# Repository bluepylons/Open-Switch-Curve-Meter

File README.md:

# About 
This is an open-source, low-cost measurement device for generating force curve measurements for MX-style switches. There are two versions - a much older Gen 1 and a newer Gen 2 design.  Force curves of various switches I've measured are in the Force curve measurements\ directory. Detailed documentation for Gen 2 is in progress and will be available [here](https://github.com/bluepylons/Open-Switch-Curve-Meter/blob/main/Gen%202%20Design/README.md).

This was designed specifically for MX switches to simplify the design and make everything cheaper and more compact, and since most of the switches I am curious about (as well as almost all new switches released today) use the MX form factor. With different switch holders it can hold other discrete switches - it was used to measure a Futaba switch, and could theoretically be used to measure Alps and other discrete swithces as well. This is not as versatile as force-curve testers built around a test stand (like [the one Haata built](https://deskthority.net/viewtopic.php?t=15133)) and can't test arbitrary keyboards like that one, but it's much cheaper to build (I spent about $200 building this, and in theory this is buildable for ~$100 if one foregoes the custom PCB and order the parts from China).

This project is licensed under the CERN OHL-S (strongly reciprocal) license for the hardware designs and the software. This is a share-alike license, and if you modify the project files you are required to also open-source your modifications. 

The force curve graphs themselves - the .ODS spreadsheets and the .PNG images of the graphs in the Force curve measurements\ folder - are licensed under [Creative Commons CC-BY 4.0](https://creativecommons.org/licenses/by/4.0/deed.en). 

# The key parts
* A linear stage. I designed around [this inexpensive $55 linear stage off Amazon](https://www.amazon.com/Sliding-Precision-Stepper-T-Shaped-Electric/dp/B07QBCG9YC/ref=sr_1_5?dchild=1&keywords=50mm%2Blinear%2Bstage&qid=1615263982&sr=8-5&th=1). You can find what appear to be identical units [on Aliexpress](https://www.aliexpress.com/item/4001272086575.html?spm=a2g0o.productlist.0.0.61906e9d3wWNyG&algo_pvid=04df7b52-bc18-4d1c-b806-9cd889c3acae&algo_expid=04df7b52-bc18-4d1c-b806-9cd889c3acae-12&btsid=0bb0623916170292735655874e869e&ws_ab_test=searchweb0_0,searchweb201602_,searchweb201603_) and elsewhere for less (if you get them from Aliexpress, make sure you buy the model with 1mm pitch (lead) on the leadscrew). Gen 2 will use the same linear stage. 
* A stepper motor. The stepper motor serves two purposes - it moves the linear stage, and also keeps track of position to plot the X-axis of the force curve. Stepper motors, as long as they aren't stalled or skip steps, move a given amount based on the number of step commands sent, and lets me forego having to directly measure position. Instead, I can just count the number of steps sent to the stepper motor, since I know how much the stepper motor will move for a given number of steps. I used the included stepper motor in the linear stage above, which moves 1.8° per step (200 steps per full rotation). Combined with the 1mm lead leadscrew on the linear stage, a single step (without microstepping) moves the switch 0.005mm. 
* A stepper motor driver. I used a Trinamic TMC2209 on Gen 1, and a Trinamic TMC2208 module on Gen 2. Communication occurs using rudimentary STEP/DIR control.  
* A load cell, to measure the force on the switch. I used [this 500g load cell](https://www.sparkfun.com/products/14728) from Sparkfun. It can be found on Aliexpress for slightly less. 
* A load cell amplifier and  ADC for reading the load cell and converting the readinging into a digital signal that can be easily read by the microcontroller. I used Avia's HX711 on both Gen 1 and Gen 2 as [Sparkfun made a module for it](https://www.sparkfun.com/products/13879), and there is an Arduino library available for it. Gen 2 has provisions for SPI and I2C for potential future upgrades with faster and more expensive ADCs (e.g. Analog Devices AD7730).
* A microcontroller. I used an Arduino Nano clone on Gen 1 and Gen 2 as I had one lying around and it's straightforward to write code for. My initial plans for Gen 2 involved using [Adafruit's Feather RP2040](https://www.adafruit.com/product/4884), though I have not had time to learn its programming language yet so I decided to spin another PCB for an Arduino Nano. 
* Software to transfer the information over to a computer. Right now, I use an Arduino 1.8.19's serial monitor to transfer the information over from the Arduino Nano clone. It's copied into a .csv file using Notepad. Cleanup of the data can be done either manually in a spreadsheet program (I use LibreOffice Calc), or can be done using [a Python script I wrote up](https://github.com/bluepylons/Open-Switch-Curve-Meter/tree/main/Processing-Python-script). Plotting is currently done with Libreoffice Calc.

There is also an RGBLED for status indication, and MX switches (2 on Gen 1, 4 on Gen 2) for control. 

The CAD was done in Alibre Atom3D. STEP files are provided. 

Gen 1 and Gen 2 both have custom PCBs, designed in KiCAD and fabbed by JLCPCB. You will need KiCAD to open the files. In theory, a PCB is not necessary - you can build this on perfboard, as off-the-shelf HX711 modules are available from [Sparkfun](https://www.sparkfun.com/products/13879) and elsewhere, and you can steper motor drivers [on breadboard-friendly breakout board](https://www.digikey.com/en/products/detail/trinamic-motion-control-gmbh/TMC2209-SILENTSTEPSTICK/10232488). However, it makes things a lot neater. 

The HX711 is powered off the microcontroller's 5V supply. The stepper motor is powered off a separate external 12V power supply.

# To do list (Gen 2)

* Documentation
	* Just like, everything
	* I'll make a video of me operating the force curve meter at some pointed
	* Write a guide on how to build one of these using off-the-shelf HX711 load cell amplifier and stepper motor modules. The PCB was done mostly for my own convenience, and it's possible to do it using off-the-shelf modules and a breadboard, though it's somewhat messier wiring wise. 
	
* Hardware
	* (eventually) Design a 3D-printed case for the PCB so that it's not exposed

* Firmware
	* Gen 2's RGBLED does not changes states like I expect to at the end of the run, so I need to debug this
	* (eventually) Write a more user-friendly UI for processing the data (the current workflow, which involves a lot of spreadsheets and copy/pasting data from Arduino Serial Monitor for both calibration and measurement, is tedious)

* Possible long-term improvements:
	* Better hosting of graphs - possibly moving off Github
		* There's something slowly in the works with various other people that currently possess force curve meters, but it will be some time before it will be up
		* We'd want something more interactive such as Plotly (which no longer takes new uploads), and something that can allow for easy comparisons between switches (e.g. overlaying graphs)
	* Some way to correct for temperature-induced drift on the load cell or amp that isn't just calibrating frequently 
		* I'm fairly annoyed by how much the load cell readings drift with temperature (simply opening a window often forces me to recalibrate), and I am considering adding additional load cell modules solely to do temperature correction (you can cancel out the temperature-dependent terms in the load cell equation if you use multiple identical load cells)/strain gauges, or doing temperature measurements and using a look up table to apply corrections or something. 
	* Possibly move away from the HX711	
		* There's a lot of sample variation among HX711's I've encountered, with some having a lot of drift and others mostly working fine. 
	
# Gen 1 Errata
* I mistakenly connected Pin 1 and Pin 2 on the Arduino on the PCB - those are the TX/RX lines, and I learned that having those connected interferes with communications between the Arduino and your computer,  and may lead to failures when uploading sketches and trying to use Serial Monitor. These lines were originally intended for uART communication with the TMC2209, but I decided to just use DIR/STEP control as it's easier to write the code. Either cut the headers off the Arduino, or do not install those pins on the socket on the PCB. 

# Thanks yous: 
* The Switchmodder [subreddit](https://www.reddit.com/r/switchmodders/) and [Discord](https://discord.gg/xnSUeETRTf)
* Nebulant and xyz for advice
* Romly, for [posting photos of their tester](https://twitter.com/Romly/status/1358983963377688579)  
* Haata, for his [incredibly useful writeup](https://deskthority.net/viewtopic.php?t=15133) on building his switch tester. 
* Gondolindrim and the [Acheron Project](http://acheronproject.com/), as I use their hotswap PCB footprint and the 3D model of the MX switch. Their open-source projects have also been very helpful for me getting into keyboard design. 
* Thank you to the following people for sending me switches to make curves of:
	* Slowshi 
	* Window Dump
	* mfchill
	* Clark
	* Aiwanei 
	* ChromePcok
	* Deadeye 
	* [Rebult Keyboards](https://www.rebultkeyboards.com/)
	* [Dangkeebs](https://dangkeebs.com/)
	* [Moyu.studio](https://moyustudio.cn/)
	* [Adobau Labs](https://adobaulabs.com/)
	* [Prevail Key Co.](https://prevailkeyco.com/)
	* Mechanicalbionicle
	* Nick7790
	* [JLabs](https://jlabs.co/)
	* Laika
	* notdoctorq
	* [Switch Oddities](https://switchoddities.com/)
	
# Links to other people with force curve meter designs and data:

* Ruddy, who's affiliated with [GeekBoards.ru](https://geekboards.ru/), independently developed a similar force curve meter and open-sourced his design on Github [here](https://github.com/geekboards/switch-force-tester). His measurements are [here](https://github.com/geekboards/switch-force-tester/tree/main/python-app/results)

* HaaTa, who founded [Input Club](https://input.club/), and well known for his force curve measurements. His design is on Github [here](https://github.com/kiibohd/force) and described on Deskthority [here](https://deskthority.net/viewtopic.php?f=62&start=&t=15133), and results are on Plotly [here](https://chart-studio.plotly.com/~haata#/)

* Nebulant and ManOfInterests also possess force curve meters, though I am not aware of any centralized location they publish their measurements. You can find their graphs on their Instagrams, across various Discord servers, Twitter, and on Keebtalk. 

* Romly built a force curve meter over in Japan. [Details here](https://romly.com/blog/c99_jikunohakari/).

* Theremingoat has a force curve meter and now has a [massive respository](https://github.com/ThereminGoat/force-curves).

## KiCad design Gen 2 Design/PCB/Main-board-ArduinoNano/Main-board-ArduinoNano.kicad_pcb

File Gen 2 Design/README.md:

# Work In Progress

**Order parts at your own risk. These files are provided as-is, and I am not responsible for any losses, harm, or damage incurred by following this guide, by ordering parts, by using the files provided, by using the resultant parts or assembled devices, or from any mistakes or errors in the files, ordering guide, or resultant parts.**

# Gen 2 

Due to the general jankiness of Gen 1, I decided to do a much neater redesign for Gen 2 back in 2021. I initially thought about [running a group buy](https://geekhack.org/index.php?topic=115453.0), though life has gotten in the way of that. I finally had some time to pick this project back up in late 2025, and am currently documenting the Gen 2 design to the point it can be easily replicated by other people. This document is very much a work in progress, though I have built and operated Gen 2. 

Mechanical CAD is done in [Alibre Atom3D](https://www.alibre.com/atom3d/), and the PCB files are done using KiCAD V9.

# ORDERING GUIDE

# Mechanicals

## Laser cut metal parts

The following parts are laser-cut out of metal. DXFs are provided [here](https://github.com/bluepylons/Open-Switch-Curve-Meter/tree/main/Gen%202%20Design/Mechanical%20files/Laser%20cut). STEP files are provided as well.

| Part name                | Material thickness         | Quantity |
| ------------------------ | -------------------------- | -------- |
| Baseplate-stand          | 3mm-3.2mm (0.118-125")     | 1        |
| Bumpon-holder            | 1.5mm-1.6mm (0.059-0.063") | 4        |
| Load-cell-mounting-plate | 3mm-3.2mm (0.118-125")     | 1        |
| Switch-plate             | 1.5mm-1.6mm (0.059-0.063") | 1        |
| Vertical plate           | 3mm-3.2mm (0.118-0.125")   | 1        |

Aluminum is generally recommended for most of the parts, though other metals (steel, brass, etc.) can work. For the baseplate stand, steel, brass, or stainless steel may be useful as the additional weight can provide more stability. All the parts on the ones I have built are cut out of aluminum 6061-T6.

Aluminum or plain steel are usually the cheapest materials. Note that steel may corrode or rust without treatment (e.g. painting, powder coating). 

In the US, I recommend [Sendcutsend](https://sendcutsend.com/). In the EU, [Laserboost](https://www.laserboost.com/) is a good source. 

For Sendcutsend, deburring is recommended, though it still tends to leave a sharp edge and may require manual deburring afterwards (with a deburring tool such as [this](https://www.mcmaster.com/4289A71/)). [Tumbling](https://sendcutsend.com/services/tumbling/) is recommended for eligible parts as it softens the edges.

## T-slotted extrusions and hardware 

I use Misumi 80/20-style extrusions, though tther brands of 20mm 80/20-style T-slotted extrusions likely work. The extrusions are tapped M5x0.8 on each end (Misumi will do this for you; the part number specifies it). However, if you have the tools you can tap it yourself to save money; you can order HFS5-2020-132 if you want to tap it yourself.

Note that nuts for other 2020 (such as McMaster or actual 80/20(R) hardware) are often incompatible as the slot opening on Misumi extrusions is a bit smaller. Be aware of this if ordering fasteners. 

| Misumi Part Number       | Description | Quantity |
| ------------------------ | ----------- | -------- |
| HFS5-2020-132-TPW        | Extrusion   | 2        |
| HNTAP5-5                 | M5 nuts     | 4        |

## 3D-printed pieces
The following parts are 3D-printed. STLs are available [here](https://github.com/bluepylons/Open-Switch-Curve-Meter/tree/main/Gen%202%20Design/Mechanical%20files/3DP).

| Part name                    | Quantity |
| ---------------------------  | -------- |
| Switch mounting bracket      | 1        |
| load-cell protection bracket | 1        |
| ADC-PCB-spacer               | 1        |
| Main-PCB-spacer              | 1        |

I have generally printed these out of PETG with a 0.2mm layer height, though other materials such as ABS and PLA are likely fine. 

## Linear actuator 

The design uses a cheap Chinese 50mm linear actuator with a 1mm pitch leadscrew. There's no exact part number for this. I ordered [this one](https://www.amazon.com/Sliding-Precision-Stepper-T-Shaped-Electric/dp/B07QBCG9YC/ref=sr_1_5?th=1) off Amazon; it is no longer available. [This](https://www.amazon.com/Linear-Actuator-Stepper-Milling-Machine/dp/B07K7FWDZJ/ref=sr_1_8?th=1) likely works as a substitute, though the counterbored mounting hole positions for the overall unit is slightly different (55mm instead of 56mm), though I have slotted the mounting holes on Vertical plate to accommodate 54-56mm. 

## Hardware

The following fasteners are needed:

| Description                               | Quantity | McMaster-Carr part number | Notes                                                     | 
| ----------------------------------------- | -------- | ------------------------- | --------------------------------------------------------- |
| M3x5 ISO 14583 Torx 10 screw              | 16       | 90362A112                 | ISO 7380 button-head (McMaster 90991A111) would also work | 
| M3x8 screw (ISO 7380 Torx T10 used)       | 4        | 90991A111                 | Pretty much any head type works as a substitute           |
| M3x10 ISO 7380 Torx T10 screw             | 12       | 90991A111                 |                                                           |
| M3x10 ISO 4762 socket head cap screw      | 6        | 91292A113                 |                                                           | 
| M3 DIN 125 washer                         | 16       | 91292A113                 |                                                           |
| M3 DIN 934 zinc-plated hex nut            | 16       | 91292A113                 | Zinc-plated instead of stainless to prevent galling       |
| M3x6 4.5-4.8mm hex Female-Female standoff | 8        | 95947A002                 | Cheaper on Digi-key                                       |
| M5x8 ISO 7380 hex socket screw            | 4        | 94500A230                 | McMaster 92095A207	also works but larger package size     |  
| M5x12 ISO 7380 hex socket screw           | 4        | 92095A210                 | Longer lengths (up to 16mm) would also work               | 

The following other hardware are needed:

| Description                               | Quantity | Notes                                                     | 
| ----------------------------------------- | -------- | --------------------------------------------------------- |
| 3M SJ-5003 bumpons (or equivalent)        | 4        | Available in different colors                             |

# PCB 

There are two PCBs, the ADC board and the Main board. The ADC board has SMT components that JLCPCB can place, while the Main board is through hole. While the project was originally going to use an Adafruit Feather RP2040 for the controller, I later switched back to using an Arduino Nano clone so I could re-use the code from Gen 1. 

The PCB can be ordered off JLCPCB using the manufacturing files provided here.

## ADC board

The following additional through-hole parts are needed:

| Reference designators | Part description            | Manufacturer | Part number     | Quantity | Notes                                               | 
| --------------------  | --------------------------- | ------------ | --------------- | -------- | --------------------------------------------------- |
| J1                    | 10-pin shrouded connector   | CNC Tech     | 3020-10-0100-00 | 1        |                                                     | 
| J2                    | 4-pin terminal block        | Würth        | 691137710004    | 1        |                                                     |
| J3                    | 2-pin terminal block        | Würth        | 691137710002    | 1        |                                                     |

D2 can be left unpopulated if D1 is populated,  but Littelfuse P4KE6.8A can be used if not (if JLCPCB is out of stock of D1, for instance)

HX711 pitfalls

## Main board

The main board can be ordered as a bare PCB, which has additional through-hole parts that need to be soldered or installed on. These parts can be sourced from Digikey, Mouser, or your electronic parts distributor of choice.

| Reference designators | Part description            | Manufacturer | Part number     | Quantity | Notes                                               | 
| --------------------  | --------------------------- | ------------ | --------------- | -------- | --------------------------------------------------- | 
| A2                    | 2.54mm 15-pin female socket | Sullins      | PPPC151LFBN-RC  | 2        | You can also cut down a longer socket               |
| A2                    | Arduino Nano or clone       | Arduino      | Nano            | 1        | Do not use the Arduino Nano Every or ESP32 versions | 
| C1, C3                | 100uF 63V capacitor         | Nichicon     | UVY1J101MPD1TD2 | 2        | 63V rating is overkill, but I had some lying around |
| D1, D3-D5             | 5.8V TVS diode DO-204AL     | Littelfuse   | P4KE6.8A        | 4        |                                                     |
| F1                    | 16V 2A polyfuse             | Bel Fuse     | 0ZRN0200FF1E    | 1        |                                                     |
| J1                    | 5.5x2.5mm barrel jack       | Kycon        | KLDX-0202-B     | 1        |                                                     |
| J2                    | 10-pin shrouded connector   | CNC Tech     | 3020-10-0100-00 | 1        |                                                     |
| J8                    | 4-pin terminal block        | Würth        | 691137710004    | 1        |                                                     |
| LED1                  | 5mm through-hole RGBLED     | Adafruit     | 1938            | 1        |                                                     |
| U2                    | 2.54mm 8-pin female socket  | Würth        | 61300811821     | 2        | You can also cut down a longer socket               |
| U2                    | TMC2208 SilentStepStick     | Watterott    | 20170003-002    | 1        | TMC2209 also works                                  |
| SW1-SW4               | Cherry MX-compatible switch | Any          | Your favorite   | 4        |                                                     |

# Electrical parts

You will need the following electrical parts as well:

| Part description                                             | Manufacturer | Part number     | Quantity | Notes                                                                 | 
| ------------------------------------------------------------ | ------------ | --------------- | -------- | --------------------------------------------------------------------- |
| 500gf TAL221 load cell                                       | Sparkfun     | 14728           | 1        | Can also be found on Aliexpress                                       | 
| 10-pin ribbon cable                                          | Assmann WSW  | H3CCH-1006G-ND  | 1        |                                                                       |
| 12V 2A power supply 5.5x2.5mm barrel jack, center positivee  | EDATEC       | ED-PSU1202-US   | 1        | Easily substituted; I use the power supply for an external hard drive |
| Alligator clip cable                                         | Adafruit     | 1008            | 1        | Easily substituted                                                    |

# Other parts

A 100g calibration weight is used to calibrate the load cell. These can easily be bought off Amazon or other places for fairly little money.

# OPERATING PROCEDURE

## Software Needed
* [Arduino IDE](https://www.arduino.cc/en/software)
* Python 3 (Jupyter Notebook) - this can be installed via a package like the [Anaconda Distribution](https://www.anaconda.com/products/distribution) of Python 3
* Libreoffice Calc
* MS Paint

## Calibration

## Measurement

## Data processing
### Automated using Python
### Manual

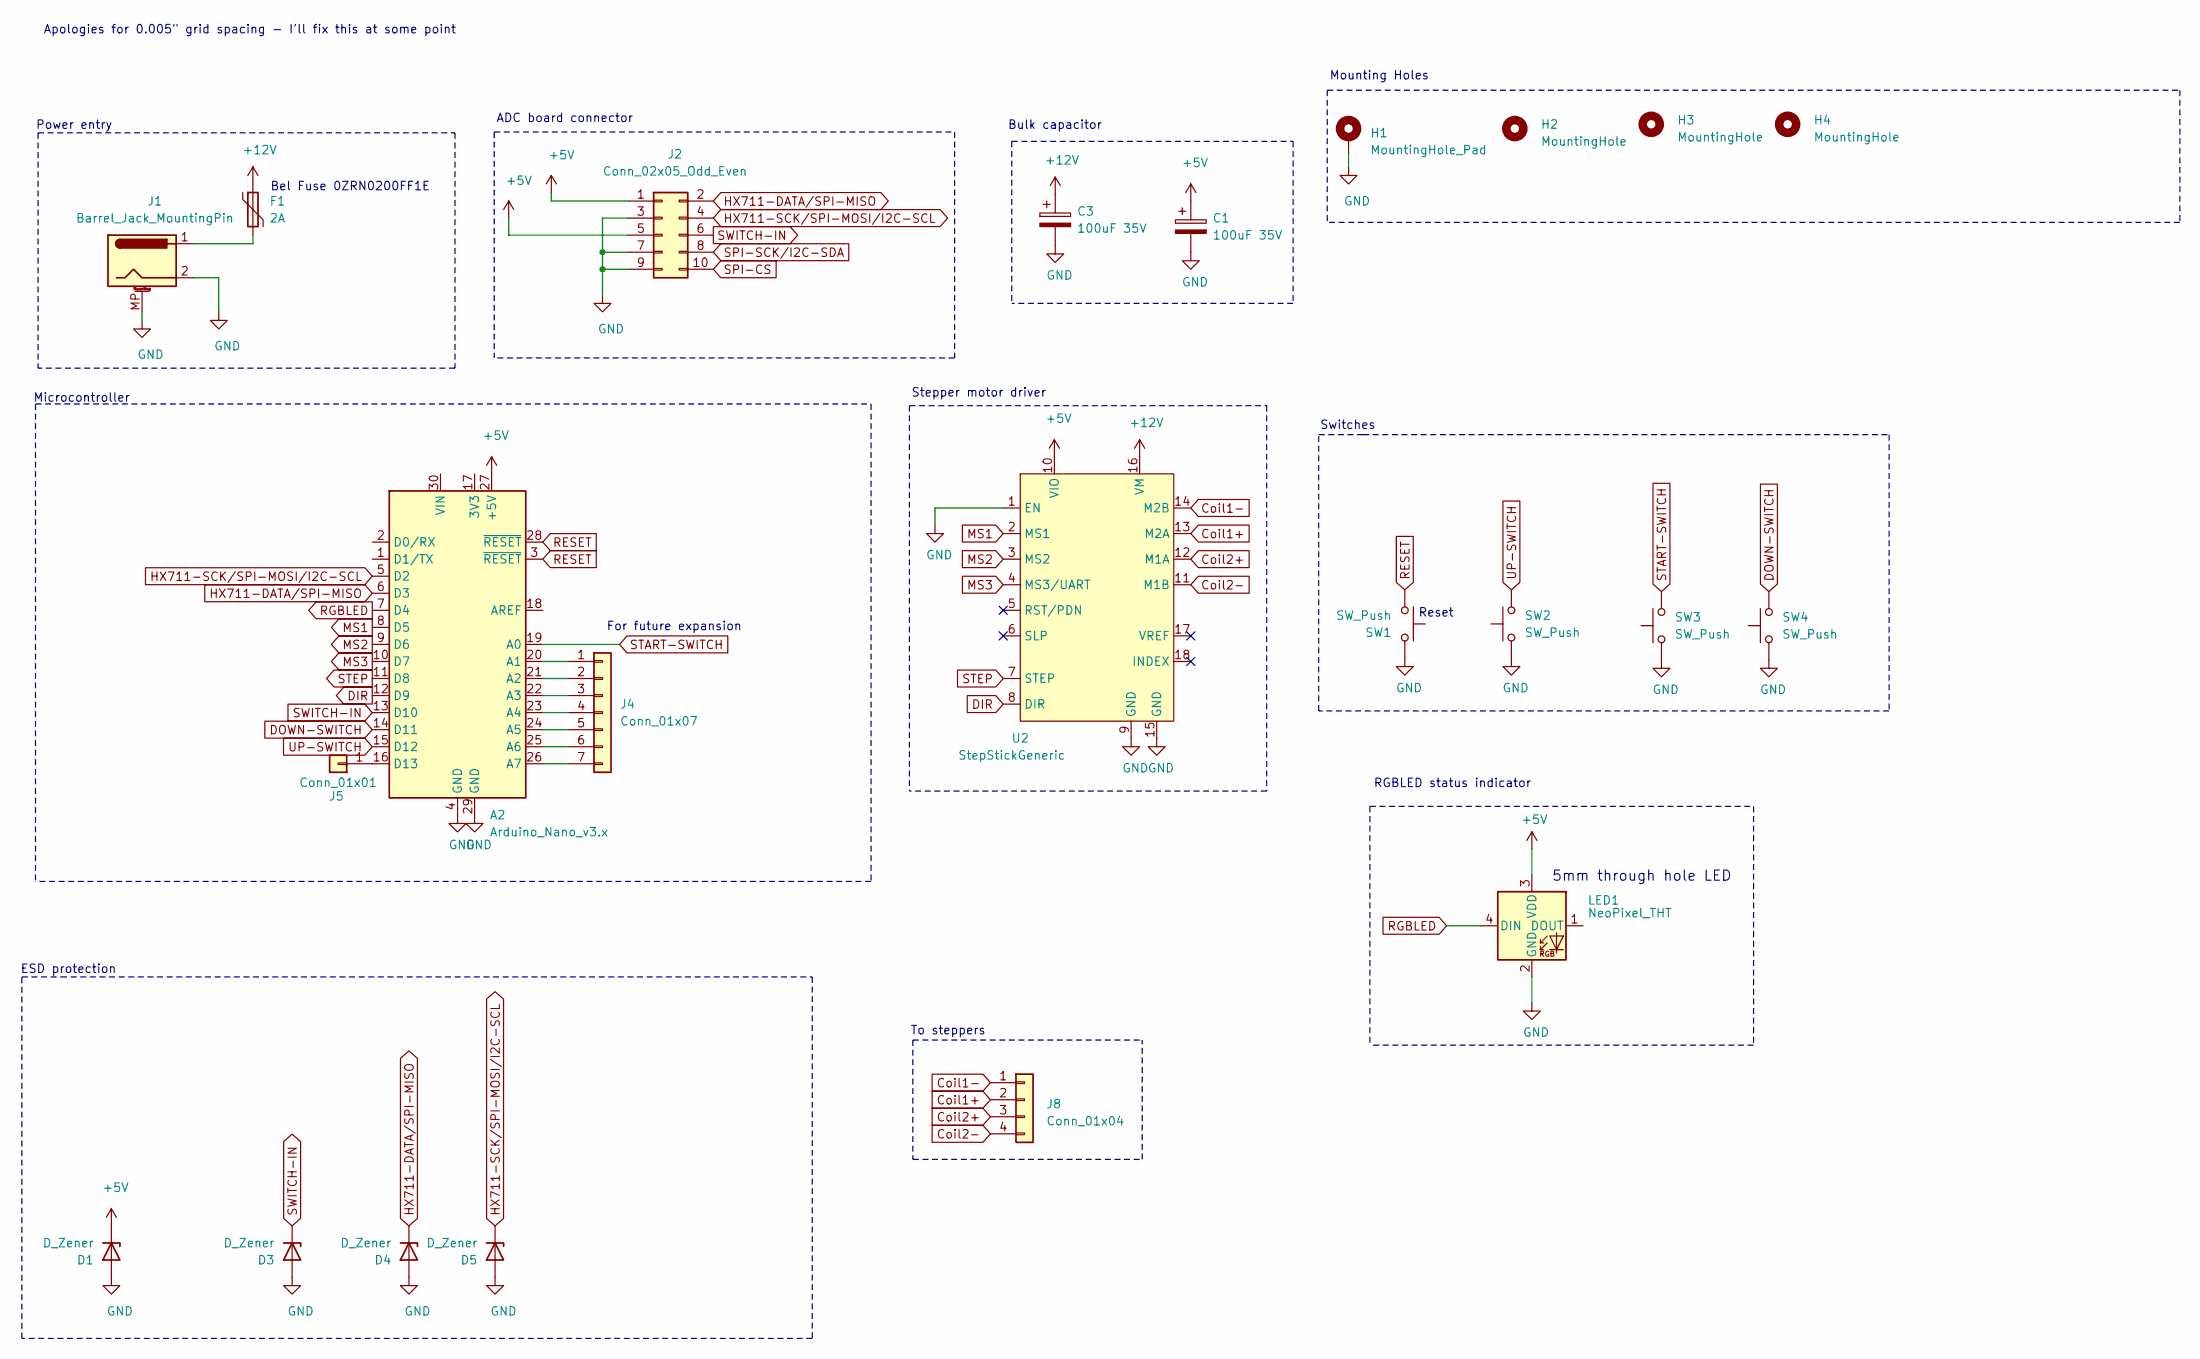
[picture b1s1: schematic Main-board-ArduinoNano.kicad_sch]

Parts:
A2: Arduino_Nano_v3.x; Arduino_Nano
C1, C3: 100uF 35V; CP_Radial_D8.0mm_P3.50mm
D1, D3, D4, D5: D_Zener; D_DO-41_SOD81_P7.62mm_Horizontal
F1: 2A; C_Disc_D10.5mm_W5.0mm_P5.00mm
H1: MountingHole_Pad; MountingHole_3.2mm_M3_ISO7380_Pad
H2, H3, H4: MountingHole; MountingHole_3.2mm_M3_ISO7380
J1: Barrel_Jack_MountingPin; BarrelJack_Horizontal
J2: Conn_02x05_Odd_Even; 2x05-P2.54mm-Shrouded-Keyed-Header
J4: Conn_01x07; PinSocket_1x07_P2.54mm_Vertical
J5: Conn_01x01; PinSocket_1x01_P2.54mm_Vertical
J8: Conn_01x04; TerminalBlock_Phoenix_MKDS-1,5-4_1x04_P5.00mm_Horizontal
LED1: NeoPixel_THT; LED_D5.0mm-4_RGB
SW1, SW2, SW3, SW4: SW_Push; SW_Cherry_MX_1.00u_PCB
U2: StepStickGeneric

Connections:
+5V: A2.27 (+5V), C1.1, D1.1 (K), J2.1, J2.5, LED1.3 (VDD), U2.10 (VIO)
+12V: C3.1, F1.1, U2.16 (VM)
Coil1+: J8.2, U2.13 (M2A)
Coil1-: J8.1, U2.14 (M2B)
Coil2+: J8.3, U2.12 (M1A)
Coil2-: J8.4, U2.11 (M1B)
DIR: A2.12 (D9), U2.8 (DIR)
DOWN-SWITCH: A2.14 (D11), SW4.2
GND: A2.4 (GND), A2.29 (GND), C1.2, C3.2, D1.2 (A), D3.2 (A), D4.2 (A), D5.2 (A), H1.1, J1.2, J1.MP (MountPin), J2.3, J2.7, J2.9, LED1.2 (GND), SW1.2, SW2.1, SW3.1, SW4.1, U2.1 (EN), U2.9 (GND), U2.15 (GND)
HX711-DATA/SPI-MISO: A2.6 (D3), D4.1 (K), J2.2
HX711-SCK/SPI-MOSI/I2C-SCL: A2.5 (D2), D5.1 (K), J2.4
MS1: A2.8 (D5), U2.2 (MS1)
MS2: A2.9 (D6), U2.3 (MS2)
MS3: A2.10 (D7), U2.4 (MS3/UART)
unnamed: A2.20 (A1), J4.1
unnamed: A2.21 (A2), J4.2
unnamed: A2.22 (A3), J4.3
unnamed: A2.23 (A4), J4.4
unnamed: A2.24 (A5), J4.5
unnamed: A2.25 (A6), J4.6
unnamed: A2.26 (A7), J4.7
unnamed: A2.16 (D13), J5.1
unnamed: F1.2, J1.1
RESET: A2.3 (~RESET), A2.28 (~RESET), SW1.1
RGBLED: A2.7 (D4), LED1.4 (DIN)
SPI-CS: J2.10
SPI-SCK/I2C-SDA: J2.8
START-SWITCH: A2.19 (A0), SW3.2
STEP: A2.11 (D8), U2.7 (STEP)
SWITCH-IN: A2.13 (D10), D3.1 (K), J2.6
UP-SWITCH: A2.15 (D12), SW2.2

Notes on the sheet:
Stepper motor driver
Bulk capacitor
Switches
Bel Fuse 0ZRN0200FF1E‎
Reset
ESD protection
For future expansion
Mounting Holes
Apologies for 0.005" grid spacing - I'll fix this at some point
RGBLED status indicator
To steppers
5mm through hole LED
Microcontroller
ADC board connector
Power entry

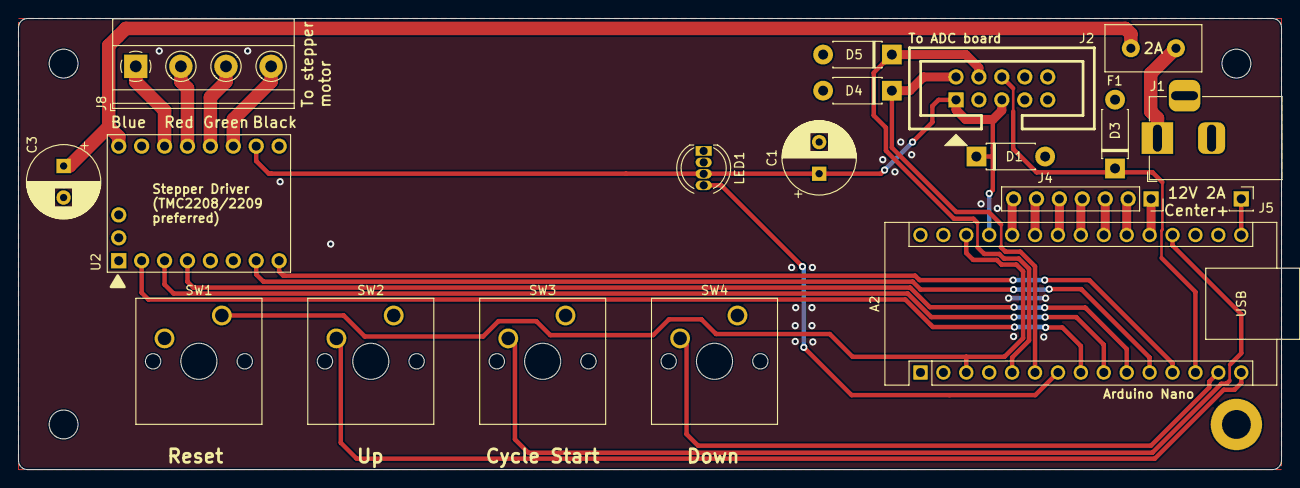
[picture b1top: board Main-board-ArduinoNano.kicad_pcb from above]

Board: 2 copper layers, 140.0 x 50.0 mm, 23 parts (0 on the bottom side), 29 nets.

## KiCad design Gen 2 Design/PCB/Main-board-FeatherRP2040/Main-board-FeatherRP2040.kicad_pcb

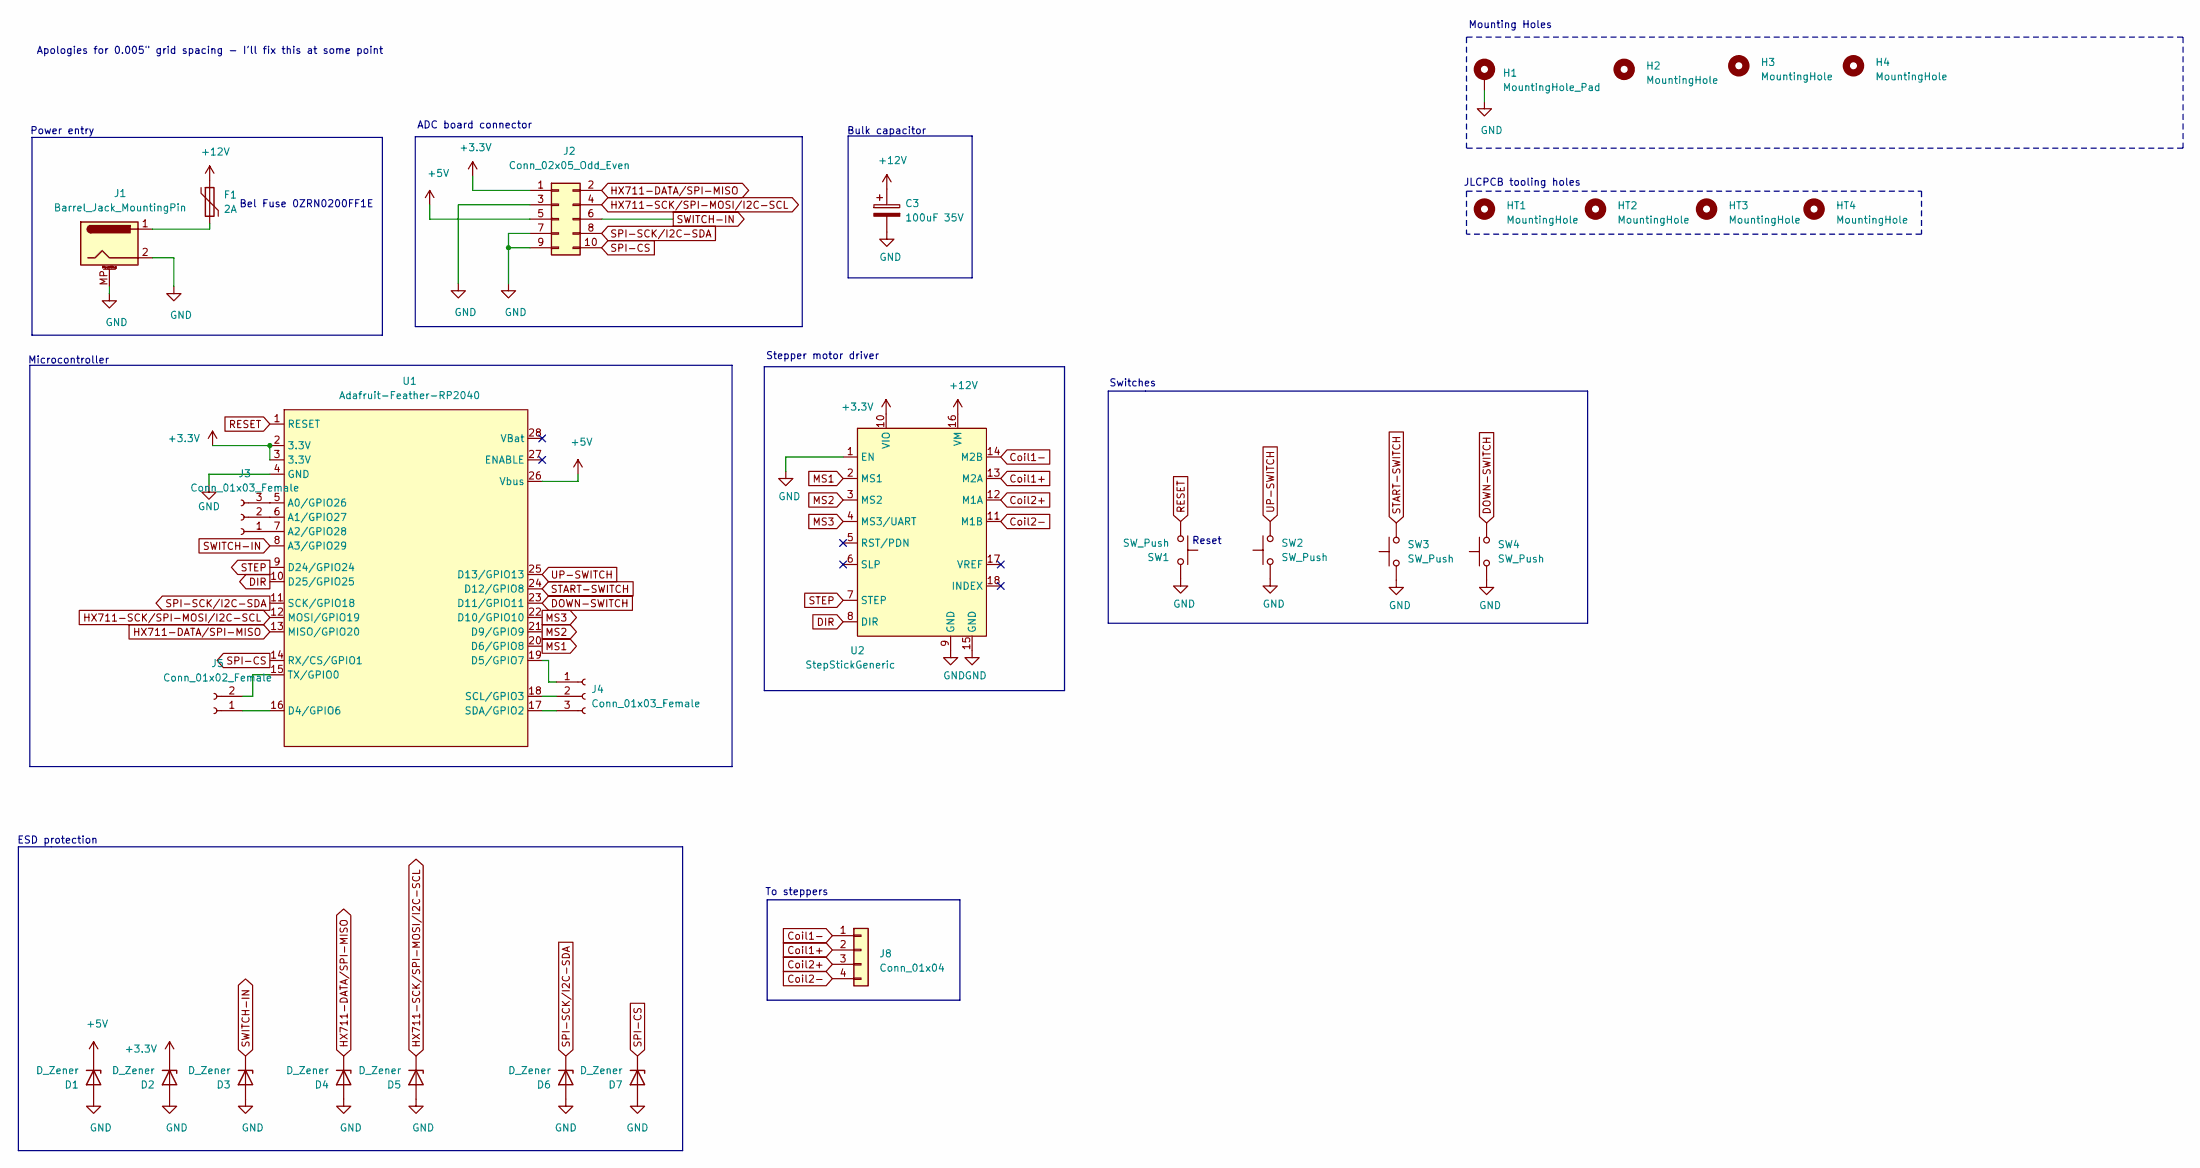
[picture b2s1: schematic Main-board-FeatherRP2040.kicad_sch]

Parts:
C3: 100uF 35V; CP_Radial_D8.0mm_P3.50mm
D1, D2, D3, D4, D5, D6, D7: D_Zener; D_DO-41_SOD81_P7.62mm_Horizontal
F1: 2A; C_Disc_D10.5mm_W5.0mm_P5.00mm
H1: MountingHole_Pad; MountingHole_3.2mm_M3_ISO7380_Pad
H2, H3, H4: MountingHole; MountingHole_3.2mm_M3_ISO7380
HT1, HT2, HT3, HT4: MountingHole; ToolingHole_1.152mm_(for_JLCPCB_SMT)
J1: Barrel_Jack_MountingPin; BarrelJack_Horizontal
J2: Conn_02x05_Odd_Even; 2x05-P2.54mm-Shrouded-Keyed-Header
J3, J4: Conn_01x03_Female; PinSocket_1x03_P2.54mm_Vertical
J5: Conn_01x02_Female; PinSocket_1x02_P2.54mm_Vertical
J8: Conn_01x04; TerminalBlock_Phoenix_MKDS-1,5-4_1x04_P5.00mm_Horizontal
SW1, SW2, SW3, SW4: SW_Push; SW_Cherry_MX_1.00u_PCB
U1: Adafruit-Feather-RP2040
U2: StepStickGeneric

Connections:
+3V3: D2.1 (K), J2.1, U1.2 (3.3V), U1.3 (3.3V), U2.10 (VIO)
+5V: D1.1 (K), J2.5, U1.26 (Vbus)
+12V: C3.1, F1.1, U2.16 (VM)
Coil1+: J8.2, U2.13 (M2A)
Coil1-: J8.1, U2.14 (M2B)
Coil2+: J8.3, U2.12 (M1A)
Coil2-: J8.4, U2.11 (M1B)
DIR: U1.10 (D25/GPIO25), U2.8 (DIR)
DOWN-SWITCH: SW4.2, U1.23 (D11/GPIO11)
GND: C3.2, D1.2 (A), D2.2 (A), D3.2 (A), D4.2 (A), D5.2 (A), D6.2 (A), D7.2 (A), H1.1, J1.2, J1.MP (MountPin), J2.3, J2.7, J2.9, SW1.2, SW2.1, SW3.1, SW4.1, U1.4 (GND), U2.1 (EN), U2.9 (GND), U2.15 (GND)
HX711-DATA/SPI-MISO: D4.1 (K), J2.2, U1.13 (MISO/GPIO20)
HX711-SCK/SPI-MOSI/I2C-SCL: D5.1 (K), J2.4, U1.12 (MOSI/GPIO19)
MS1: U1.20 (D6/GPIO8), U2.2 (MS1)
MS2: U1.21 (D9/GPIO9), U2.3 (MS2)
MS3: U1.22 (D10/GPIO10), U2.4 (MS3/UART)
unnamed: F1.2, J1.1
unnamed: J3.1, U1.7 (A2/GPIO28)
unnamed: J3.2, U1.6 (A1/GPIO27)
unnamed: J3.3, U1.5 (A0/GPIO26)
unnamed: J4.1, U1.19 (D5/GPIO7)
unnamed: J4.2, U1.18 (SCL/GPIO3)
unnamed: J4.3, U1.17 (SDA/GPIO2)
unnamed: J5.1, U1.16 (D4/GPIO6)
unnamed: J5.2, U1.15 (TX/GPIO0)
RESET: SW1.1, U1.1 (RESET)
SPI-CS: D7.1 (K), J2.10, U1.14 (RX/CS/GPIO1)
SPI-SCK/I2C-SDA: D6.1 (K), J2.8, U1.11 (SCK/GPIO18)
START-SWITCH: SW3.2, U1.24 (D12/GPIO8)
STEP: U1.9 (D24/GPIO24), U2.7 (STEP)
SWITCH-IN: D3.1 (K), J2.6, U1.8 (A3/GPIO29)
UP-SWITCH: SW2.2, U1.25 (D13/GPIO13)

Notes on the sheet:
Stepper motor driver
JLCPCB tooling holes
Bulk capacitor
Switches
Bel Fuse 0ZRN0200FF1E‎
Reset
ESD protection
Mounting Holes
Apologies for 0.005" grid spacing - I'll fix this at some point
To steppers
Microcontroller
ADC board connector
Power entry

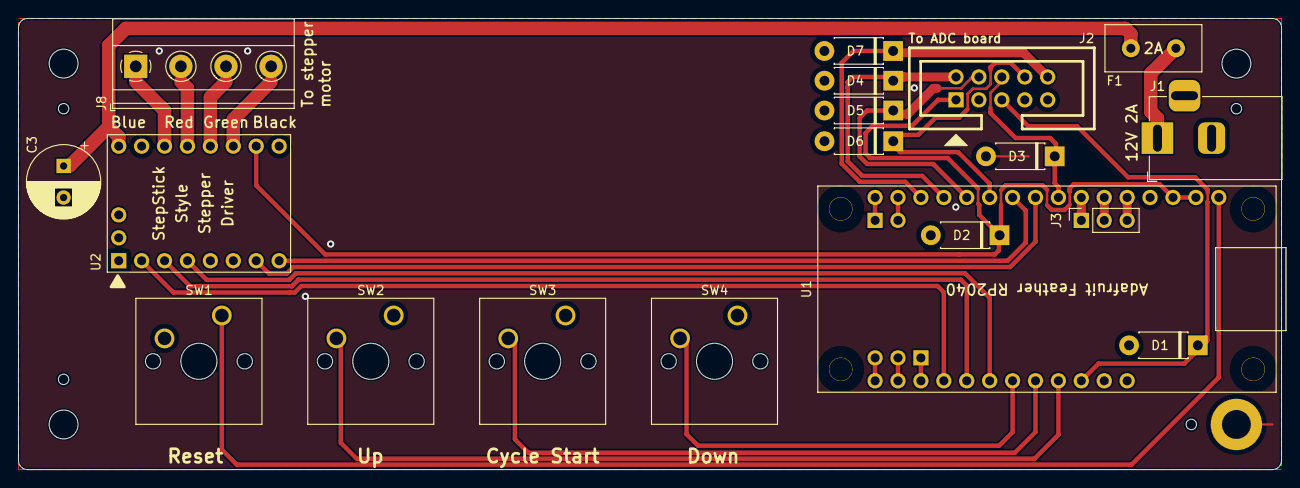
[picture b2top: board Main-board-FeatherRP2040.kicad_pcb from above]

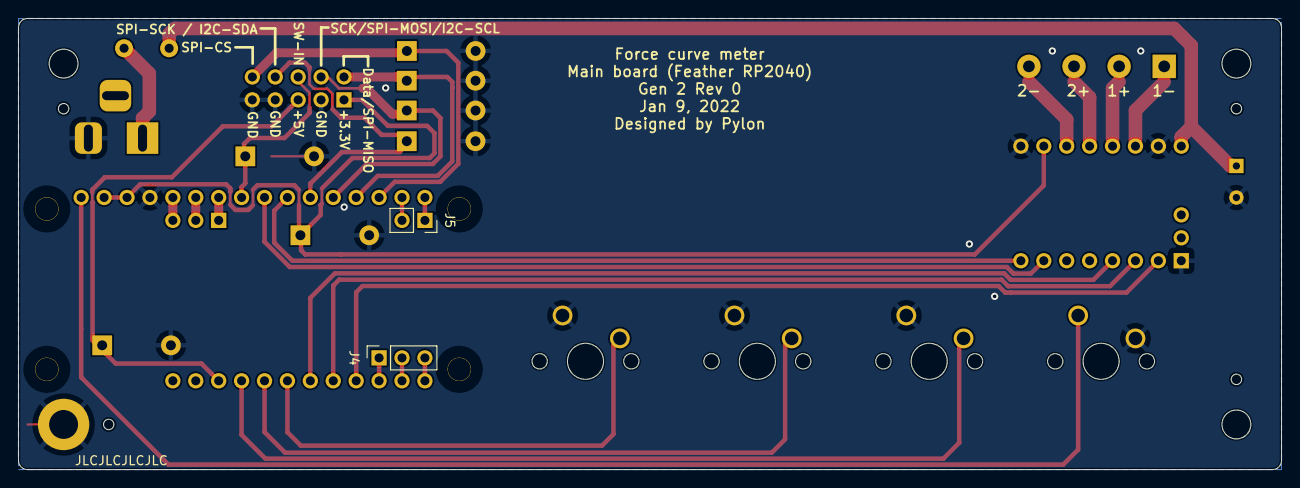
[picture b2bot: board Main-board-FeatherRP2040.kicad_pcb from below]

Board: 2 copper layers, 140.0 x 50.0 mm, 29 parts (2 on the bottom side), 31 nets.

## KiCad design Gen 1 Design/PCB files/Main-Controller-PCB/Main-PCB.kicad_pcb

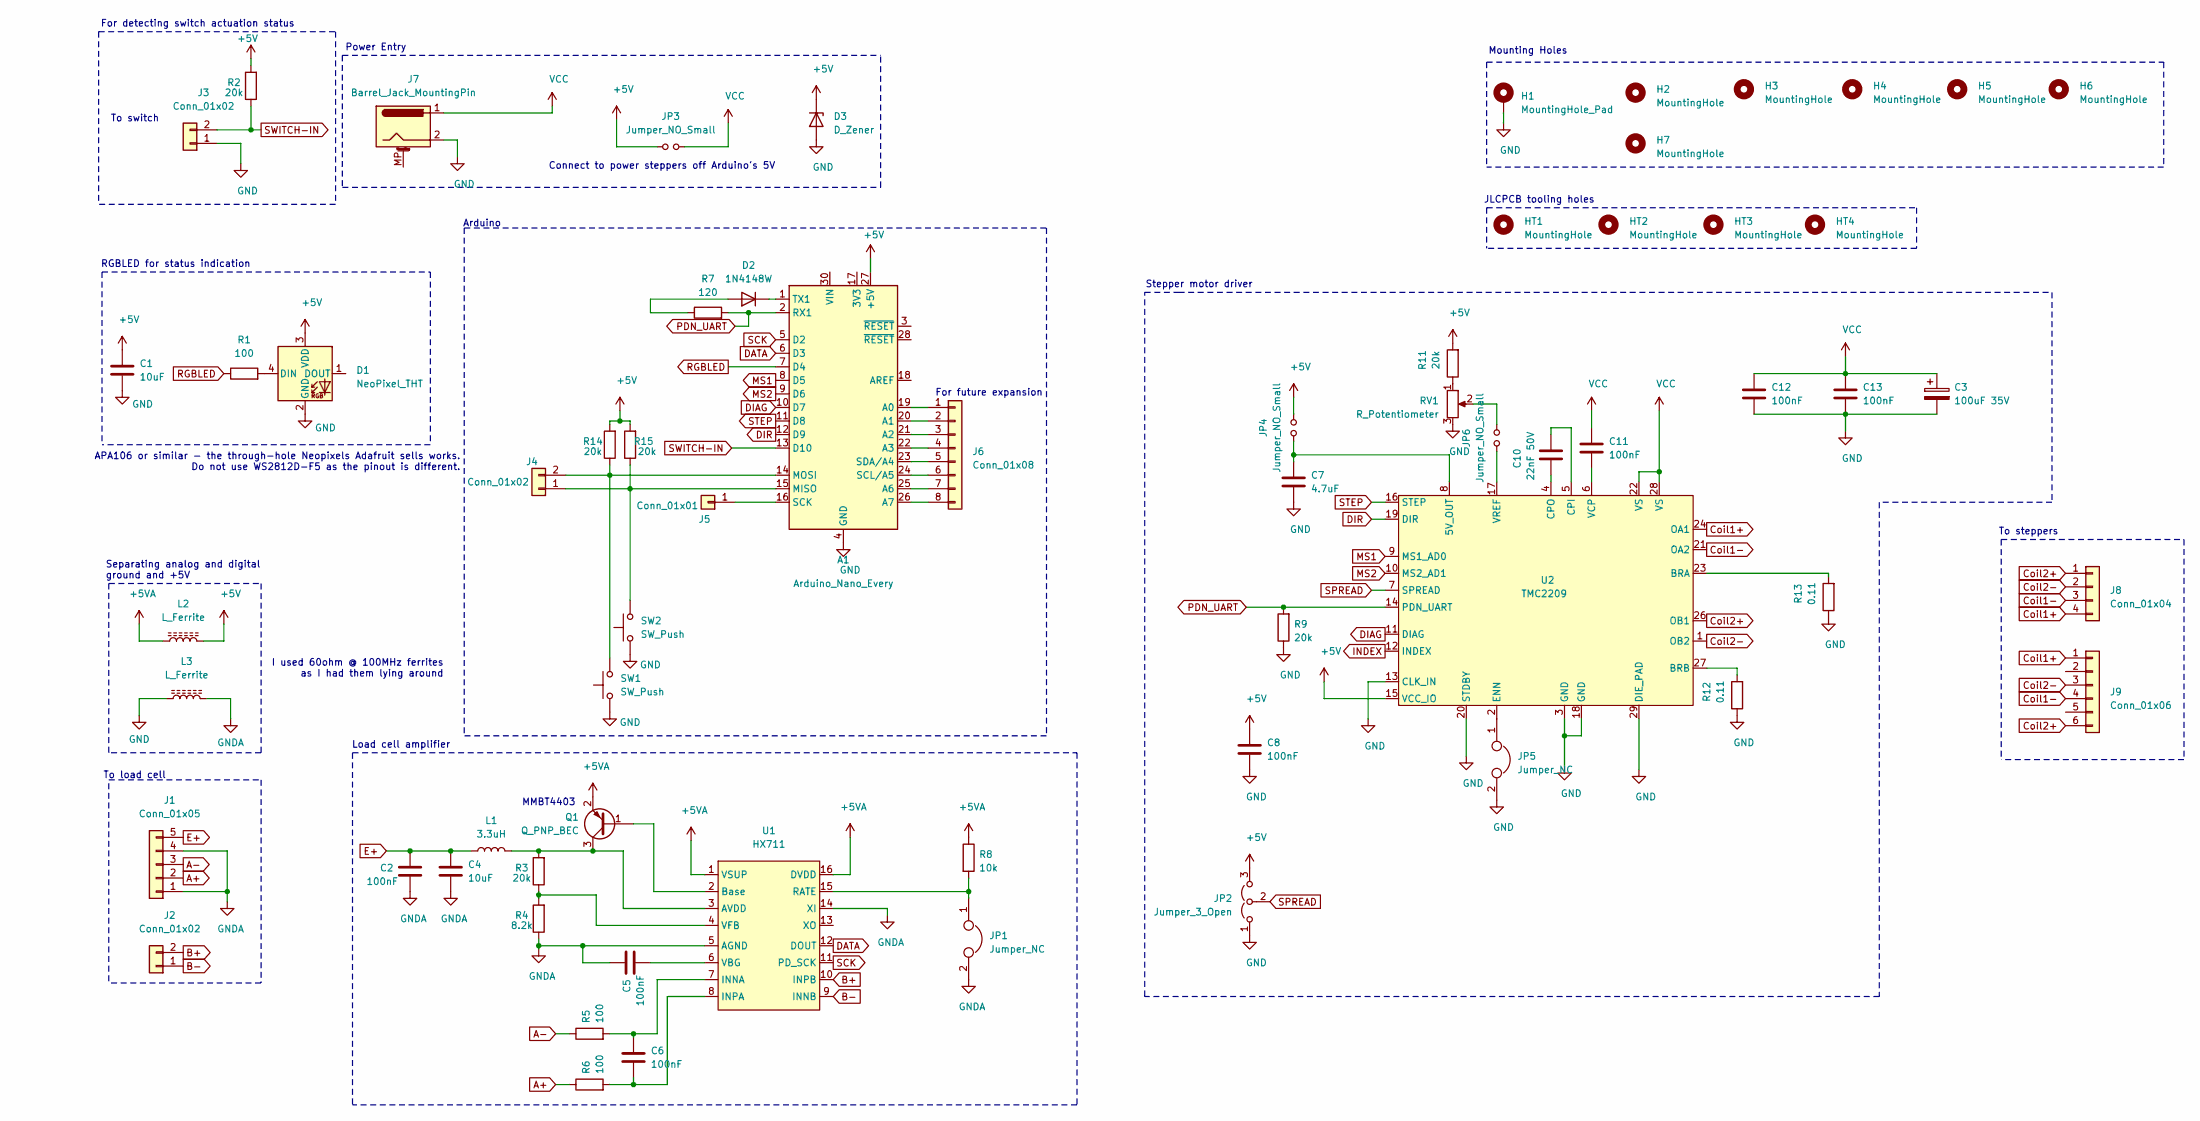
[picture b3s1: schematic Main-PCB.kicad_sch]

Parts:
A1: Arduino_Nano_Every; Arduino_Nano
C1, C4: 10uF; C_0805_2012Metric_Pad1.18x1.45mm_HandSolder
C2, C5, C6, C8, C11, C12, C13: 100nF; C_0805_2012Metric_Pad1.18x1.45mm_HandSolder
C3: 100uF 35V; CP_Radial_D8.0mm_P3.50mm
C7: 4.7uF; C_0805_2012Metric_Pad1.18x1.45mm_HandSolder
C10: 22nF 50V; C_0805_2012Metric_Pad1.18x1.45mm_HandSolder
D1: NeoPixel_THT; LED_D5.0mm-4_RGB
D2: 1N4148W; D_SOD-123
D3: D_Zener; D_SOD-323
H1: MountingHole_Pad; MountingHole_5.3mm_M5_ISO7380_Pad
H2, H7: MountingHole; MountingHole_5.3mm_M5_ISO7380
H3, H4, H5, H6: MountingHole; MountingHole_3.2mm_M3_ISO7380
HT1, HT2, HT3, HT4: MountingHole; ToolingHole_1.152mm_(for_JLCPCB_SMT)
J1: Conn_01x05; PinSocket_1x05_P2.54mm_Vertical
J2, J3, J4: Conn_01x02; PinSocket_1x02_P2.54mm_Vertical
J5: Conn_01x01; PinSocket_1x01_P2.54mm_Vertical
J6: Conn_01x08; PinSocket_1x08_P2.54mm_Vertical
J7: Barrel_Jack_MountingPin; BarrelJack_Horizontal
J8: Conn_01x04; JST_XH_B4B-XH-A_1x04_P2.50mm_Vertical
J9: Conn_01x06; JST_PH_B6B-PH-K_1x06_P2.00mm_Vertical
JP1, JP5: Jumper_NC; SolderJumper-2_P1.3mm_Bridged_Pad1.0x1.5mm
JP2: Jumper_3_Open; SolderJumper-3_P2.0mm_Open_TrianglePad1.0x1.5mm
JP3, JP4, JP6: Jumper_NO_Small; SolderJumper-2_P1.3mm_Open_TrianglePad1.0x1.5mm
L1: 3.3uH; L_0805_2012Metric_Pad1.15x1.40mm_HandSolder
L2, L3: L_Ferrite; L_0805_2012Metric_Pad1.15x1.40mm_HandSolder
Q1: Q_PNP_BEC; SOT-23_Handsoldering
R1, R5, R6: 100; R_0805_2012Metric_Pad1.20x1.40mm_HandSolder
R2, R3, R9, R11, R14, R15: 20k; R_0805_2012Metric_Pad1.20x1.40mm_HandSolder
R4: 8.2k; R_0805_2012Metric_Pad1.20x1.40mm_HandSolder
R7: 120; R_0805_2012Metric_Pad1.20x1.40mm_HandSolder
R8: 10k; R_0805_2012Metric_Pad1.20x1.40mm_HandSolder
R12, R13: 0.11; R_1206_3216Metric_Pad1.42x1.75mm_HandSolder
RV1: R_Potentiometer; Potentiometer_Runtron_RM-065_Vertical
SW1, SW2: SW_Push; SW_Cherry_MX_1.00u_PCB
U1: HX711; SOP-16_3.9x9.9mm_P1.27mm
U2: TMC2209; QFN-28-1EP_5x5mm_P0.5mm_EP3.35x3.35mm

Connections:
+5V: A1.27 (+5V), C1.1, C8.1, D1.3 (VDD), D3.1 (K), JP2.3 (B), JP3.1, JP4.2, L2.2, R2.2, R11.2, R14.2, R15.2, U2.15 (VCC_IO)
+5VA: L2.1, Q1.2 (E), R8.1, U1.1 (VSUP), U1.16 (DVDD)
A+: J1.2, R6.1
A-: J1.3, R5.1
B+: J2.2, U1.10 (INPB)
B-: J2.1, U1.9 (INNB)
Coil1+: J8.4, J9.1, U2.24 (OA1)
Coil1-: J8.3, J9.4, U2.21 (OA2)
Coil2+: J8.1, J9.6, U2.26 (OB1)
Coil2-: J8.2, J9.3, U2.1 (OB2)
DATA: A1.6 (D3), U1.12 (DOUT)
DIAG: A1.10 (D7), U2.11 (DIAG)
DIR: A1.12 (D9), U2.19 (DIR)
E+: C2.1, C4.1, J1.5, L1.1
GND: A1.4 (GND), A1.29 (GND), C1.2, C3.2, C7.2, C8.2, C12.2, C13.2, D1.2 (GND), D3.2 (A), H1.1, J3.1, J7.2, JP2.1 (A), JP5.2, L3.1, R9.1, R12.1, R13.1, RV1.3, SW1.1, SW2.1, U2.3 (GND), U2.13 (CLK_IN), U2.18 (GND), U2.20 (STDBY), U2.29 (DIE_PAD)
GNDA: C2.2, C4.2, C5.1, J1.1, J1.4, JP1.2, L3.2, R4.1, U1.5 (AGND), U1.14 (XI)
INDEX: U2.12 (INDEX)
MS1: A1.8 (D5), U2.9 (MS1_AD0)
MS2: A1.9 (D6), U2.10 (MS2_AD1)
unnamed: A1.1 (TX1), D2.1 (K)
unnamed: A1.16 (SCK), J5.1
unnamed: A1.19 (A0), J6.1
unnamed: A1.20 (A1), J6.2
unnamed: A1.21 (A2), J6.3
unnamed: A1.22 (A3), J6.4
unnamed: A1.23 (SDA/A4), J6.5
unnamed: A1.24 (SCL/A5), J6.6
unnamed: A1.25 (A6), J6.7
unnamed: C5.2, U1.6 (VBG)
unnamed: C6.1, R5.2, U1.7 (INNA)
unnamed: C6.2, R6.2, U1.8 (INPA)
unnamed: C10.1, U2.4 (CPO)
unnamed: C10.2, U2.5 (CPI)
unnamed: C11.2, U2.6 (VCP)
unnamed: D1.4 (DIN), R1.2
unnamed: D2.2 (A), R7.1
unnamed: A1.26 (A7), J6.8
unnamed: JP1.1, R8.2, U1.15 (RATE)
unnamed: JP6.1, U2.17 (VREF)
unnamed: JP6.2, RV1.2
unnamed: L1.2, Q1.3 (C), R3.2, U1.3 (AVDD)
unnamed: Q1.1 (B), U1.2 (Base)
unnamed: R3.1, R4.2, U1.4 (VFB)
unnamed: R11.1, RV1.1
unnamed: R12.2, U2.27 (BRB)
unnamed: R13.2, U2.23 (BRA)
unnamed: A1.14 (MOSI), J4.2, R14.1, SW1.2
unnamed: A1.15 (MISO), J4.1, R15.1, SW2.2
unnamed: JP5.1, U2.2 (ENN)
unnamed: C7.1, JP4.1, U2.8 (5V_OUT)
PDN_UART: A1.2 (RX1), R7.2, R9.2, U2.14 (PDN_UART)
RGBLED: A1.7 (D4), R1.1
SCK: A1.5 (D2), U1.11 (PD_SCK)
SPREAD: JP2.2 (C), U2.7 (SPREAD)
STEP: A1.11 (D8), U2.16 (STEP)
SWITCH-IN: A1.13 (D10), J3.2, R2.1
VCC: C3.1, C11.1, C12.1, C13.1, J7.1, JP3.2, U2.22 (VS), U2.28 (VS)

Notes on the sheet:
To switch
Stepper motor driver
JLCPCB tooling holes
To load cell
Mounting Holes
Arduino
To steppers
Connect to power steppers off Arduino's 5V
Separating analog and digital ground and +5V
Power Entry
Load cell amplifier
APA106 or similar - the through-hole Neopixels Adafruit sells works. Do not use WS2812D-F5 as the pinout is different.
For future expansion
For detecting switch actuation status
MMBT4403
RGBLED for status indication
I used 60ohm @ 100MHz ferrites as I had them lying around
